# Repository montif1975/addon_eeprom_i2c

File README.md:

# addon_eeprom_i2c
Schematic, PCB and construction files (gerber) for add-on with eeprom Microchip 24LC256 using I2C interface.

The project contains two folders:
- eeprom_i2c is the add-on schematic and single PCB
- epprom_i2c_panel is the multi-PCB construction file (4 PCB in a single frame)

The project is made with KiCad 9.0.

The resulting PCB is:

The multi-PCB frame is:

I printed and mounted some samples, here an image of the PCB:

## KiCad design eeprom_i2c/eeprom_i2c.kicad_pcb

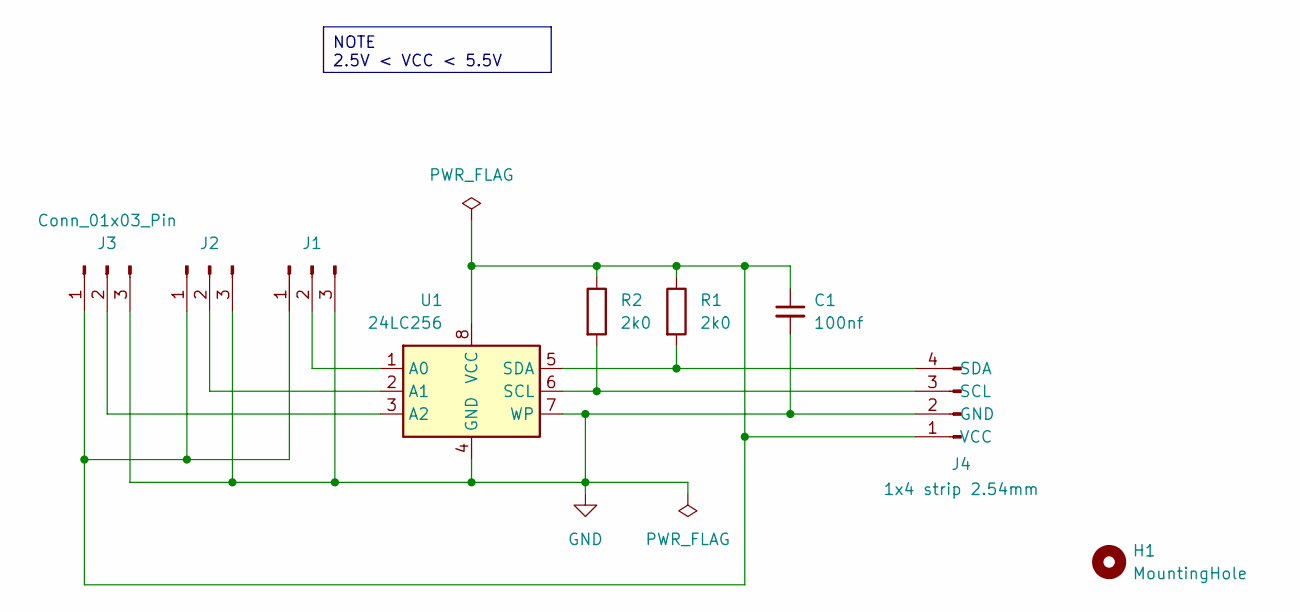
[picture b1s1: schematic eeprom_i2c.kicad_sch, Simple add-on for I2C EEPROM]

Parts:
C1: 100nf; C_Disc_D3.0mm_W2.0mm_P2.50mm
H1: MountingHole; MountingHole_3.2mm_M3
J1, J2, J3: Conn_01x03_Pin; PinHeader_1x03_P2.54mm_Vertical
J4: 1x4 strip 2.54mm; PinHeader_1x04_P2.54mm_Vertical
R1, R2: 2k0; R_Axial_DIN0207_L6.3mm_D2.5mm_P7.62mm_Horizontal
U1: 24LC256; DIP-8_W7.62mm

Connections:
GND: C1.2, J1.3, J2.3, J3.3, J4.2 (GND), U1.4 (GND), U1.7 (WP)
unnamed: C1.1, J1.1, J2.1, J3.1, J4.1 (VCC), R1.1, R2.1, U1.8 (VCC)
unnamed: J1.2, U1.1 (A0)
unnamed: J2.2, U1.2 (A1)
unnamed: J3.2, U1.3 (A2)
unnamed: J4.3 (SCL), R2.2, U1.6 (SCL)
unnamed: J4.4 (SDA), R1.2, U1.5 (SDA)

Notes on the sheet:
NOTE 2.5V < VCC < 5.5V

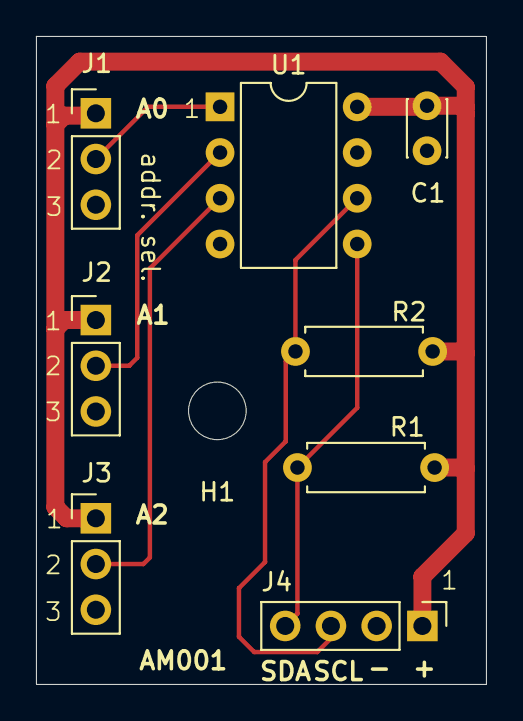
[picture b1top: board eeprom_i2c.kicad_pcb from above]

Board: 2 copper layers, 25.0 x 36.0 mm, 9 parts (0 on the bottom side), 7 nets.

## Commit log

2025-03-02 Create project
2025-03-02 Add gitignore
2025-03-02 Update gitignore
2025-03-02 Update gitignore (another change)
2025-03-02 Backup files removed
2025-03-02 Update README.md (2)
2025-03-15 Add by-pass capacitor; add mounting hole and change main connector's pinout.
2025-03-16 Change the position of C1 (close to Vcc PIN of U1). Add gerber for F_Mask e B_Mask.
2025-03-16 Update panel for production and fix label position (gerber regenerated).
2025-05-03 Updated README and add photo of the PCB printed and assembled.
